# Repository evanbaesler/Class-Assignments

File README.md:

# Class Assignments
Projects made for courses.

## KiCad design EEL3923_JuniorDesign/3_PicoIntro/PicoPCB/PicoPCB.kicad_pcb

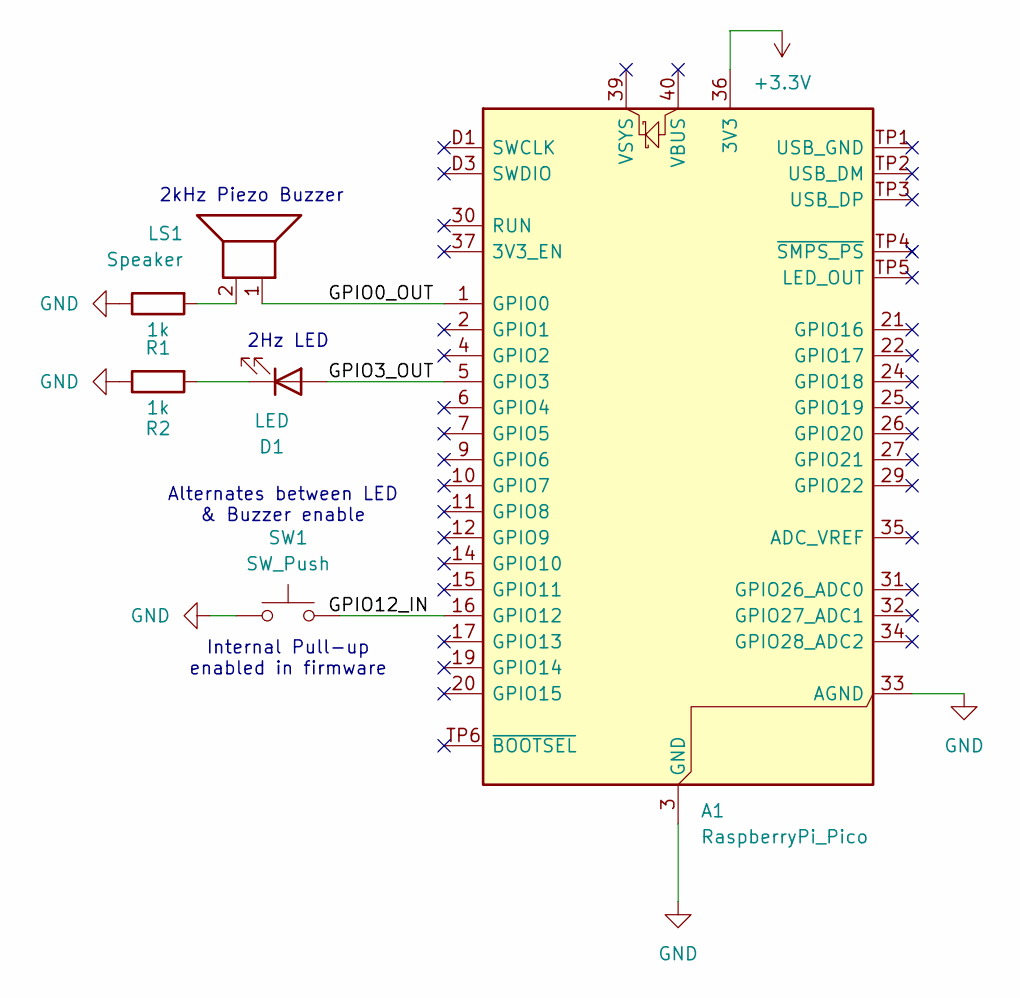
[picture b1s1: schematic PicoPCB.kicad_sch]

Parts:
A1: RaspberryPi_Pico; RaspberryPi_Pico_SMD
D1: LED; LED_D1.8mm_W1.8mm_H2.4mm_Horizontal_O1.27mm_Z1.6mm
LS1: Speaker; Buzzer_TDK_PS1240P02BT_D12.2mm_H6.5mm
R1, R2: 1k; R_Axial_DIN0411_L9.9mm_D3.6mm_P7.62mm_Vertical
SW1: SW_Push; SW_Push_1P1T_NO_CK_PTS125Sx43PSMTR

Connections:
+3.3V: A1.36 (3V3)
/GPIO0_OUT: A1.1 (GPIO0), LS1.1
/GPIO3_OUT: A1.5 (GPIO3), D1.2 (A)
GND: A1.3 (GND), A1.8 (GND), A1.13 (GND), A1.18 (GND), A1.23 (GND), A1.28 (GND), A1.33 (AGND), A1.38 (GND), A1.D2 (GND), R1.1, R2.1, SW1.1
unnamed: A1.16 (GPIO12), SW1.2
unnamed: D1.1 (K), R2.2
unnamed: LS1.2, R1.2

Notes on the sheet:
2kHz Piezo Buzzer
Internal Pull-up enabled in firmware
2Hz LED
Alternates between LED & Buzzer enable

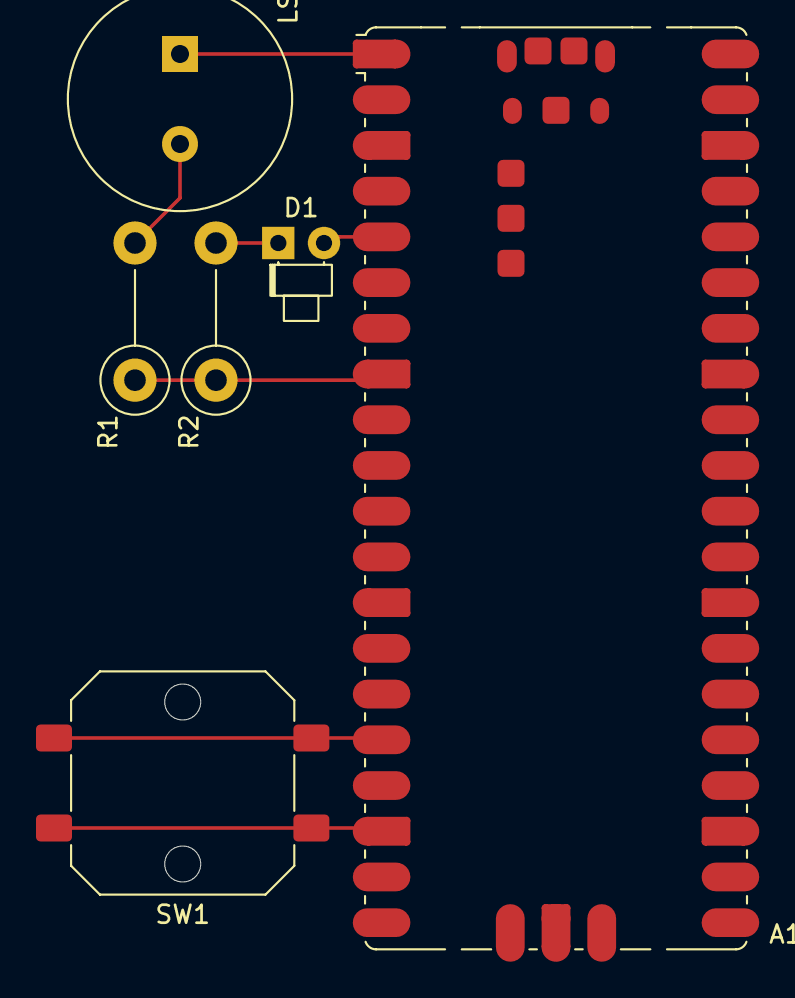
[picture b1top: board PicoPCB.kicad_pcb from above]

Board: 2 copper layers, 6 parts (0 on the bottom side), 6 nets.

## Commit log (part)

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2025-06-01 Initialization
    Started my Github adventure!
2025-06-02 C++ Finalized
    Finished C++ of V = IR Calculator
2025-06-02 C++ and Python V=IR Calculator
    Final Submission of V = IR calculator included with this commit.
2025-06-16 Group Project + Assignment 3
2025-06-16 Organizing Github and learning VSCode
2025-06-16 Laptop Sync
2025-06-16 Set Up MinGW Template for Duplication -- Migrating to VSCode.
    I finally set up MinGW to work with VSCode in the repository by making a template of .vscode and a renamable .cpp file. For the time being this works, and will be mighty useful to start taking advant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
2025-06-26 Created Structure-based data entry for a City Temperature Logger project.
    As title suggests, this includes a commit for a new project where we used structures in C++ and the equivalent in Python to make a program that allows you to add cities, their temperatures, and calcu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
2025-07-08 Note Logger Creation
    Brought the Note Logger python script into the repository.
2025-07-09 Note Logger Completion
    Here I added a program that is capable of logging notes, allows you to compare priorities, view all notes, mark as completed, and view how many notes / completed notes in total.
2025-07-28 String Practice Update
2025-09-20 Added MATLAB assignments to repository.
    As title suggests, I am adding my current signals and systems homework and lab work for the semester.
2025-09-20 Finished the Fourier Synthesis
    Project imagined a lone scientist working to synthesize a complex waveform from its components using individual data points, their harmonic frequency, and designated k values.
    Determined the net waveform, along with it's DC offset by finding the real value of a_0.
    Was fun!
2025-09-27 Start BuildingTraceData Lab
    Started the lab to separate a waveform into its components based on a built trace data generated via student ID.
2025-09-27 Ignore
2025-10-04 Lab 5
    Constructs .wav files from notes using open source constructors.
2025-10-04 Finished Lab 4
2025-10-05 Finished Lab 5 (Audio Constructor)
    Audio Constructor using open-source software to generate .wav files that play a tune, using either synthesizer sounds or simulating a trumpet.
2025-10-11 Added Lab 6 (Developing Images from Signals)
    Adding Lab 6 to be completed later tonight, framework for building images by defining pixels as a matrix with positions of x and y, and defining their grayscale value as z.
2025-10-11 General Update
    Completed HW #2 MATLAB, and accidentally saved the useWheneverQuizzes file.
2025-11-15 Sync
    Syncing to work from desktop.
2025-11-15 Sync 2
    Working from desktop
2026-01-18 Update
    Resyncing Github for the new semester.
2026-01-29 EML Files and updates.
2026-05-28 Lets start using this thing again!
    I have started Microprocessor Applications 1, the best documentation will likely be found in the Digital Logic and MicroP1 classes. Electronic Circuits may have some documentation although less thoro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
2026-05-28 Some more updates from my PC!
    See name!
2026-06-02 Lab 2: GPIO Finished!
    In this lab we learn the basics of assembly GPIO for the ATxmega128A1U. Our final creation for this section is an animation creator/player, where the user can store up to 8000 frames in storage. Play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
